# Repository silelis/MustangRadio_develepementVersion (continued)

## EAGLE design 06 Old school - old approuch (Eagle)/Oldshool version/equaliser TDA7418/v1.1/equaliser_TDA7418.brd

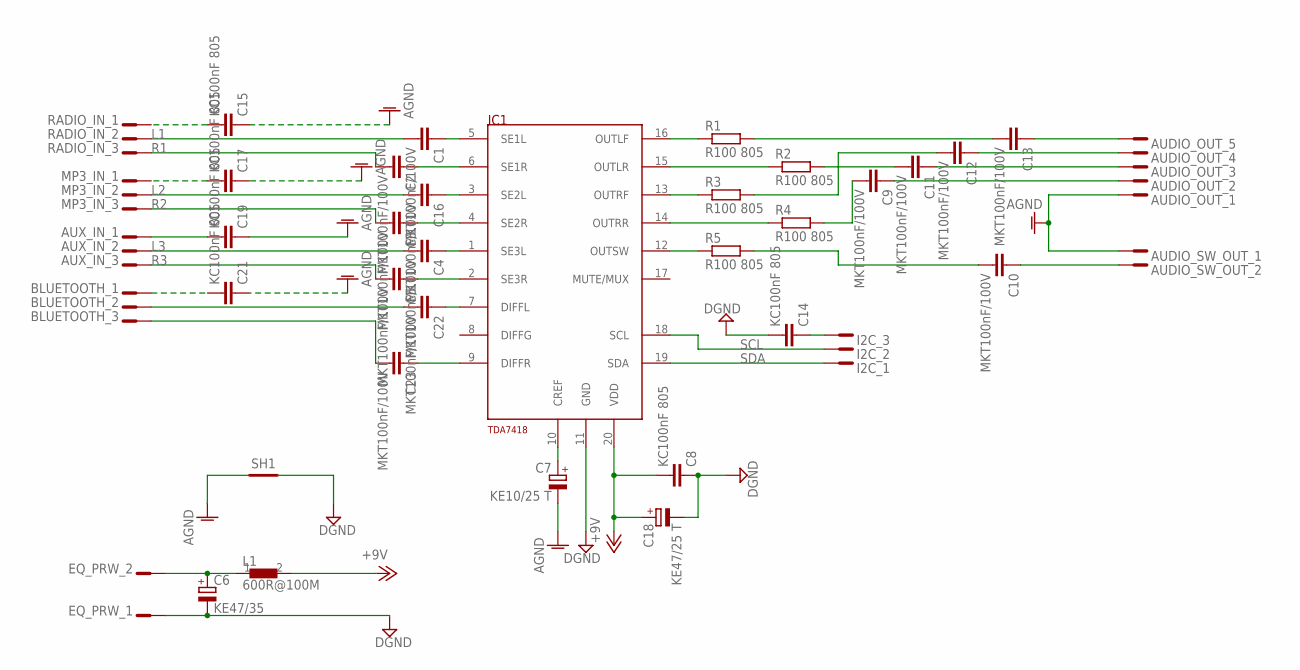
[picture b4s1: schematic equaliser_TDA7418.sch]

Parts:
AUDIO_OUT: JST_5_PIN_B5B-PH-KS; B5B-PH-KS
AUDIO_SW_OUT: JST_2_PIN_B2B-PH-KS; B2B-PH-KS
AUX_IN: JST_3_PIN_B3B-PH-KS; B3B-PH-KS
BLUETOOTH: JST_3_PIN_B3B-PH-KS; B3B-PH-KS
C1, C2, C3, C4, C5, C9, C10, C11, C12, C13, C16, C22, C23: MKT100nF/100V; C050-035X075
C6: KE47/35; TT2D6
C7: KE10/25 T; E1,8-4
C8, C14, C15, C17, C19, C21: KC100nF 805; C0805
C18: KE47/25 T; B45181B
EQ_PRW: JST_2_PIN_B2B-XH-A; B2B-XH-A
I2C: JST_3_PIN_B3B-PH-KS; B3B-PH-KS
IC1: TDA7418; SO20
L1: 600R@100M; R0805
MP3_IN: JST_3_PIN_B3B-PH-KS; B3B-PH-KS
R1, R2, R5: R100 805; R0805
R3, R4: R100 805; M0805
RADIO_IN: JST_3_PIN_B3B-PH-KS; B3B-PH-KS
SH1: SHORT-HT5; SHORT_TOP-50

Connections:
+9V0: C8.2, C18.+, IC1.20 (VDD), L1.2
AGND: AUDIO_OUT.P$1, AUDIO_SW_OUT.P$1, C7.-, C15.1, C17.1, C19.1, C21.1, SH1.1
DGND: C6.-, C8.1, C14.2, C18.-, EQ_PRW.P$1, IC1.11 (GND), SH1.2
L1: C1.2, RADIO_IN.P$2
L2: C16.2, MP3_IN.P$2
L3: AUX_IN.P$2, C4.2
unnamed: C6.+, EQ_PRW.P$2, L1.1
unnamed: AUDIO_OUT.P$2, C9.1
unnamed: C7.+, IC1.10 (CREF)
unnamed: C1.1, IC1.5 (SE1L)
unnamed: C2.1, IC1.6 (SE1R)
unnamed: C16.1, IC1.3 (SE2L)
unnamed: C3.1, IC1.4 (SE2R)
unnamed: C4.1, IC1.1 (SE3L)
unnamed: C5.1, IC1.2 (SE3R)
unnamed: C10.2, R5.2
unnamed: AUDIO_SW_OUT.P$2, C10.1
unnamed: IC1.16 (OUTLF), R1.1
unnamed: IC1.15 (OUTLR), R2.1
unnamed: C12.2, R3.2
unnamed: C11.2, R2.2
unnamed: IC1.13 (OUTRF), R3.1
unnamed: C9.2, R4.2
unnamed: IC1.14 (OUTRR), R4.1
unnamed: IC1.12 (OUTSW), R5.1
unnamed: AUDIO_OUT.P$3, C11.1
unnamed: AUDIO_OUT.P$4, C12.1
unnamed: AUDIO_OUT.P$5, C13.1
unnamed: C14.1, I2C.P$3
unnamed: C15.2, RADIO_IN.P$1
unnamed: C13.2, R1.2
unnamed: C17.2, MP3_IN.P$1
unnamed: AUX_IN.P$1, C19.2
unnamed: BLUETOOTH.P$1, C21.2
unnamed: C22.1, IC1.7 (DIFFL)
unnamed: C23.1, IC1.9 (DIFFR)
unnamed: BLUETOOTH.P$2, C22.2
unnamed: BLUETOOTH.P$3, C23.2
R1: C2.2, RADIO_IN.P$3
R2: C3.2, MP3_IN.P$3
R3: AUX_IN.P$3, C5.2
SCL: I2C.P$2, IC1.18 (SCL)
SDA: I2C.P$1, IC1.19 (SDA)

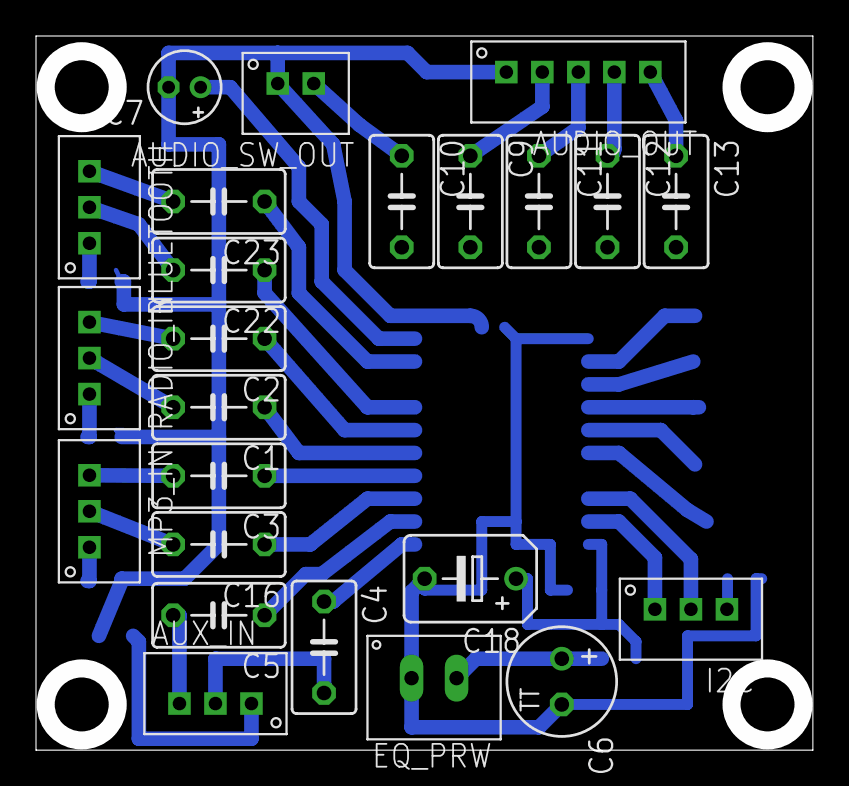
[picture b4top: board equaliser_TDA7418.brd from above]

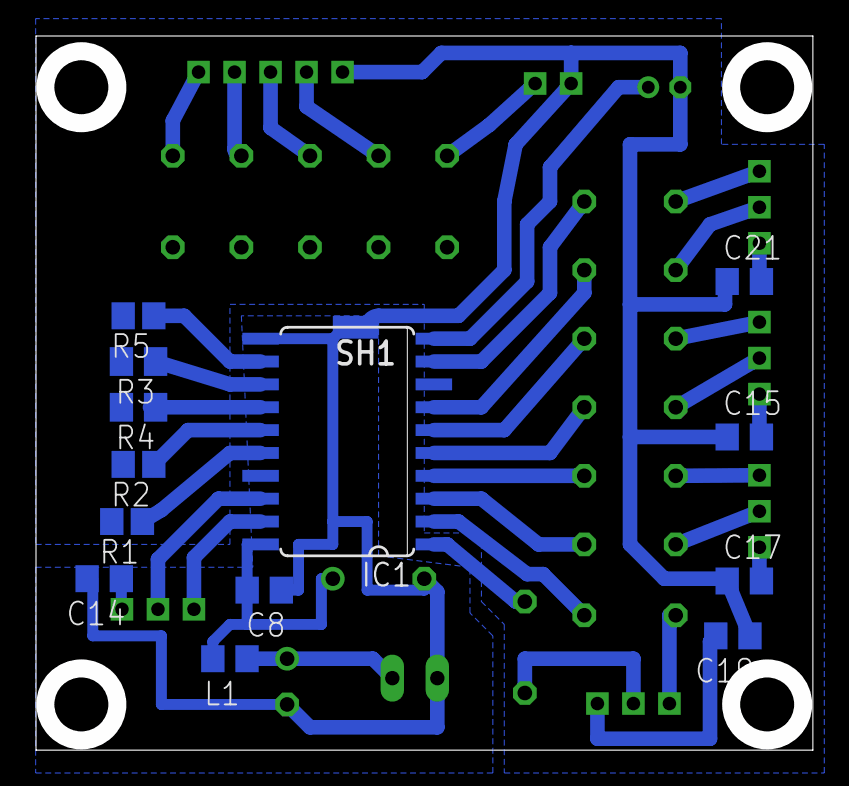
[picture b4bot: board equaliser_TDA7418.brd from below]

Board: 2 copper layers, 43.2 x 39.7 mm, 38 parts (14 on the bottom side), 43 nets.

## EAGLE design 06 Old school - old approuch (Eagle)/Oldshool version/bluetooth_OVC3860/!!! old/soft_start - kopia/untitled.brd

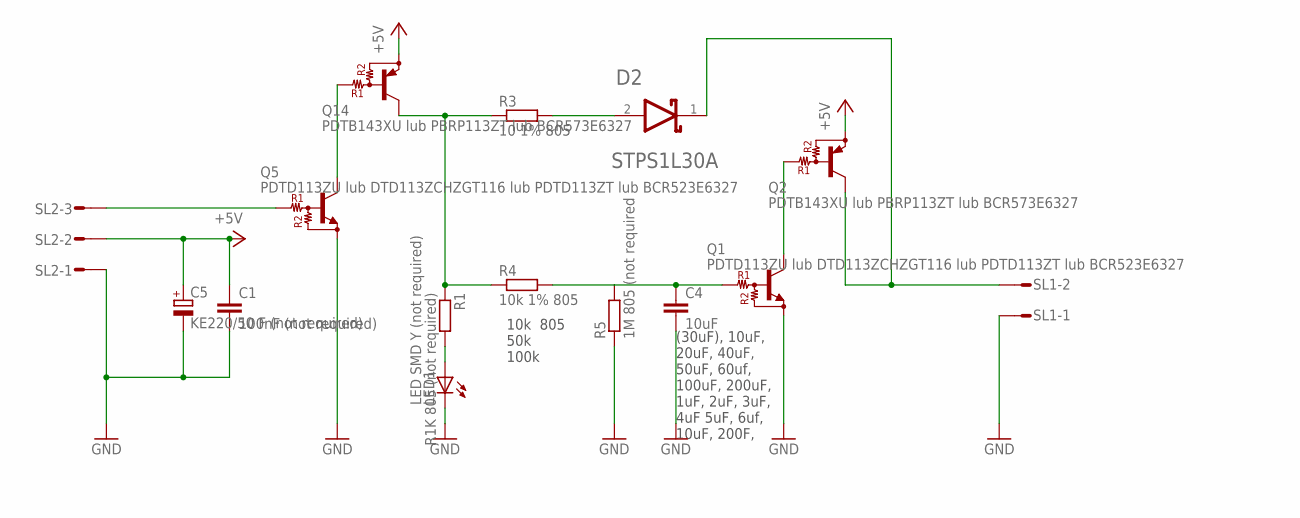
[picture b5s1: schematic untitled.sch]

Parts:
C1: 100nF (not required); C0805
C4: 10uF; C0805
C5: KE220/50 F (not required); PANASONIC_G
D2: MBR0530T1G, STPS1L30A lub STPS1L30U; STMICROELECTRONICS_STPS1L30A_0
LED1: LED SMD Y (not required); CHIP-LED0805
Q1, Q5: PDTD113ZU lub DTD113ZCHZGT116 lub PDTD113ZT lub B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; SOT-23
Q2, Q14: PDTB143XU lub PBRP113ZT lub BCR573E6327; SOT-23
R1: R1K 805 (not required); R0805
R3: 10 1% 805; M0805
R4: 10k 1% 805; M0805
R5: 1M 805 (not required; M0805
SL1: M02S; 02P
SL2: M03S; 03P

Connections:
+5V: C1.1, C5.+, Q2.2 (E), Q14.2 (E), SL2.2
GND: C1.2, C4.2, C5.-, LED1.C, Q1.2 (E), Q5.2 (E), R5.1, SL1.1, SL2.1
unnamed: Q1.3 (C), Q2.1 (B)
unnamed: LED1.A, R1.2
unnamed: Q14.3 (C), R1.1, R3.1, R4.1
unnamed: D2.2 (ANODE), R3.2
unnamed: Q5.1 (B), SL2.3
unnamed: Q5.3 (C), Q14.1 (B)
unnamed: C4.1, Q1.1 (B), R4.2, R5.2
SOFT_START_5.0V: D2.1 (CATHODE), Q2.3 (C), SL1.2

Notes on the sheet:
10k 805 50k 100k
(30uF), 10uF, 20uF, 40uF, 50uF, 60uf, 100uF, 200uF, 1uF, 2uF, 3uF, 4uF 5uF, 6uf, 10uF, 200F,

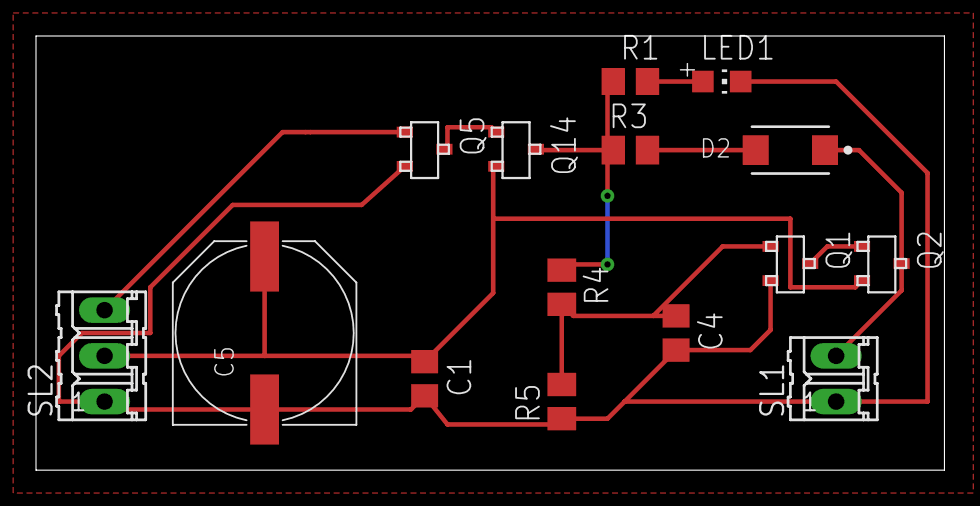
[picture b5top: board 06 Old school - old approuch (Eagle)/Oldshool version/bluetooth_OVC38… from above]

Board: 2 copper layers, 50.5 x 24.1 mm, 15 parts (0 on the bottom side), 10 nets.

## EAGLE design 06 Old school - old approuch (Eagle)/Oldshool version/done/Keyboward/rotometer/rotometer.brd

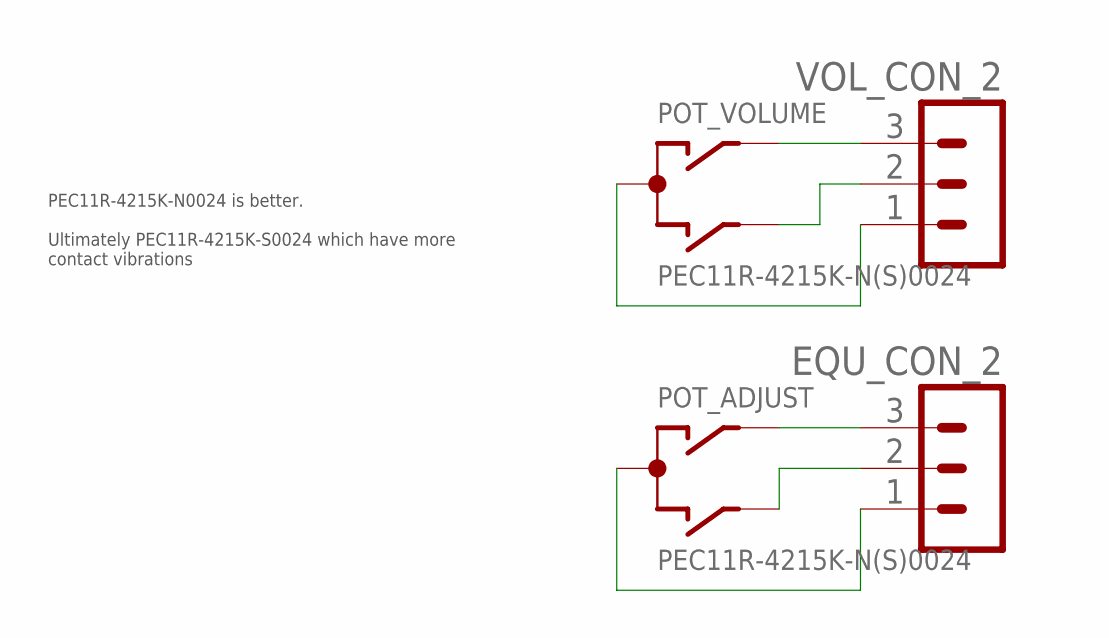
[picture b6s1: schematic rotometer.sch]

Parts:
EQU_CON_2: MA03-1
POT_ADJUST: PEC11R-4215K-N(S)0024; ALPS_EC12E_SW
POT_VOLUME: PEC11R-4215K-N(S)0024; ALPS_EC12E_SW
VOL_CON_2: MA03-1

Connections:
EQU_GND: EQU_CON_2.1, POT_ADJUST.C
unnamed: POT_VOLUME.B, VOL_CON_2.2
unnamed: POT_VOLUME.A, VOL_CON_2.3
unnamed: EQU_CON_2.3, POT_ADJUST.A
unnamed: EQU_CON_2.2, POT_ADJUST.B
VOL_GND: POT_VOLUME.C, VOL_CON_2.1

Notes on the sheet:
PEC11R-4215K-N0024 is better. Ultimately PEC11R-4215K-S0024 which have more contact vibrations

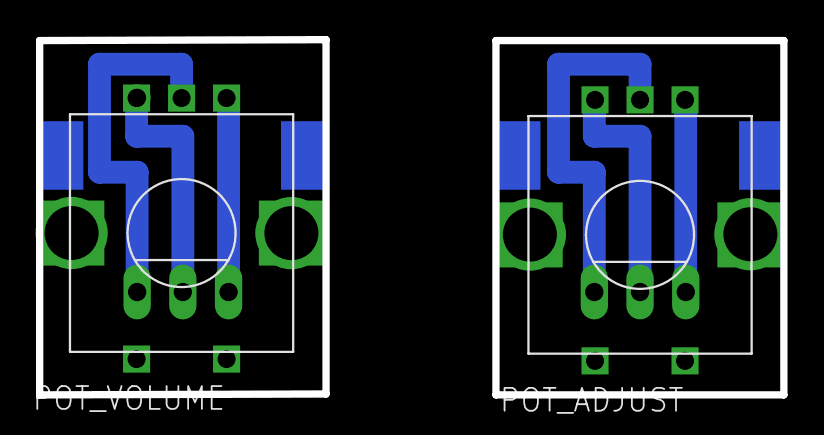
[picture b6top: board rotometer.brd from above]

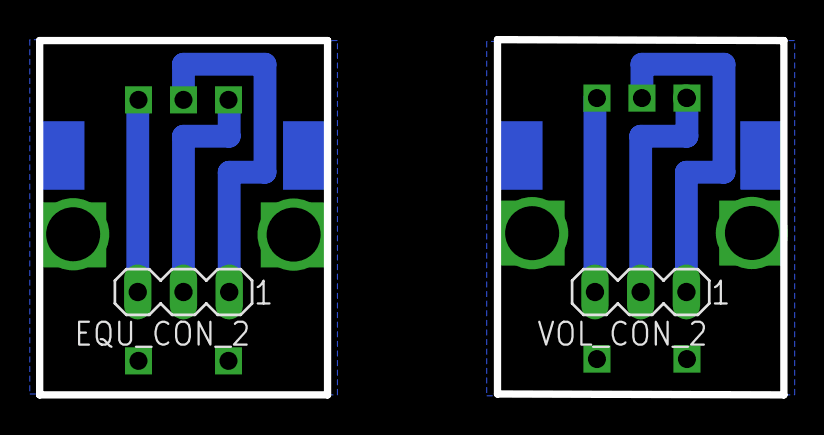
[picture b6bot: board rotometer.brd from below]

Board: 2 copper layers, 41.3 x 19.7 mm, 4 parts (2 on the bottom side), 6 nets.

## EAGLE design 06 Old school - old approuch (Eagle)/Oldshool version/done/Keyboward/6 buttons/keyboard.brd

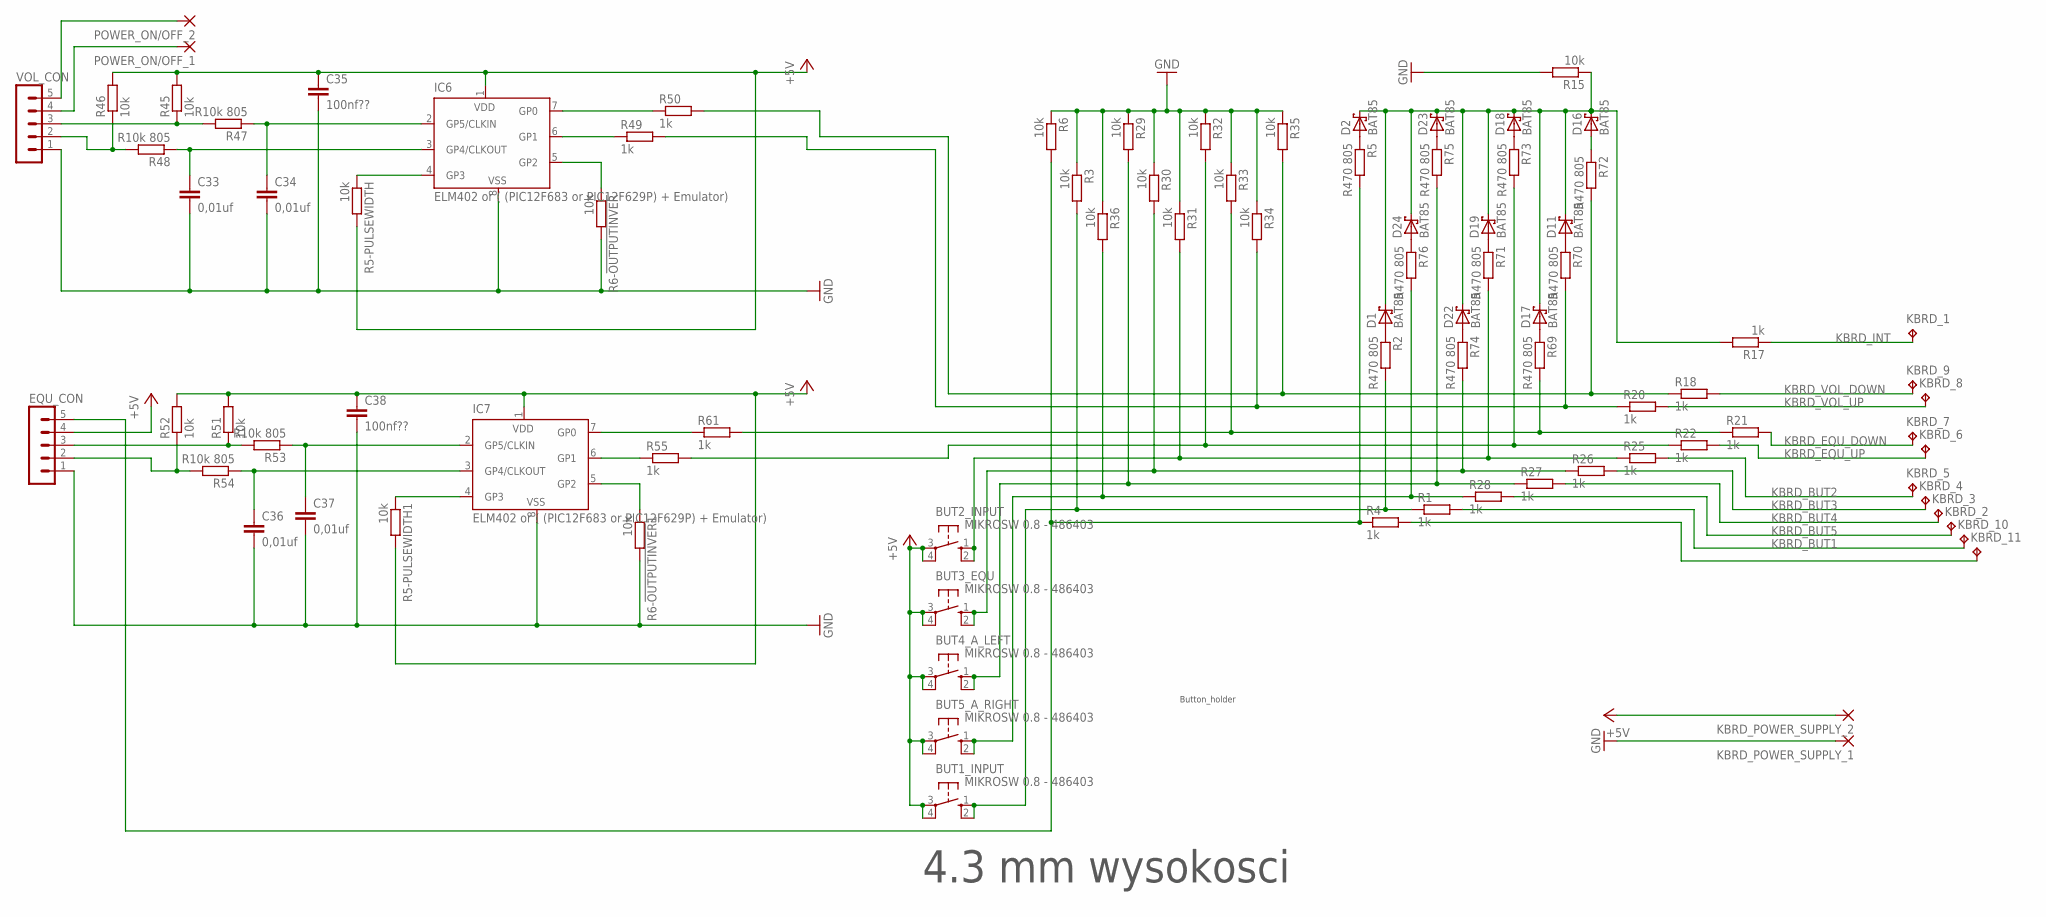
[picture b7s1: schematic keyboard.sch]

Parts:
BUT1_INPUT, BUT2_INPUT, BUT3_EQU, BUT4_A_LEFT, BUT5_A_RIGHT: MIKROSW 0.8 - 486403; B3F-10XX; MPN B3F-1000
C33, C34, C36, C37: 0,01uf; C0805
C35, C38: 100nf??; C0805
D1, D2, D11, D16, D17, D18, D19, D22, D23, D24: BAT85; DO34-5
EQU_CON: MA05-1
IC6, IC7: ELM402 or ( (PIC12F683 or PIC12F629P) + Emulator); DIL8; MPN PIC12F629-E/P
KBRD_1, KBRD_2, KBRD_3, KBRD_4, KBRD_5, KBRD_6, KBRD_7, KBRD_8, KBRD_9, KBRD_10, KBRD_11: TPPAD1-13Y; P1-13Y
KBRD_POWER_SUPPLY_1, KBRD_POWER_SUPPLY_2: 1,6/0,9
POWER_ON/OFF_1, POWER_ON/OFF_2: 2,15/1,0
R1, R4, R17, R18, R20, R21, R22, R25, R26, R27, R28, R49, R50, R55, R61: 1k; R0805
R2, R5, R69, R70, R71, R72, R73, R74, R75, R76: R470 805; R0805
R3, R6-!OUTPUTINVER!, R6-!OUTPUTINVER!1, R15, R29, R30, R36, R45, R46: 10k; R0805
R5-PULSEWIDTH, R5-PULSEWIDTH1: 10k; 0204/7
R6, R32, R33, R34, R35: 10k; 0204/5
R31, R51, R52: 10k; M0805
R47, R48, R53, R54: R10k 805; R0805
U$1: TRZYMADLO; TRZYMADLO_POPYCHACZY
VOL_CON: MA05-1

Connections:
+5V: BUT1_INPUT.3, BUT1_INPUT.4 (P1), BUT2_INPUT.3, BUT2_INPUT.4 (P1), BUT3_EQU.3, BUT3_EQU.4 (P1), BUT4_A_LEFT.3, BUT4_A_LEFT.4 (P1), BUT5_A_RIGHT.3, BUT5_A_RIGHT.4 (P1), C35.1, C38.1, EQU_CON.4, IC6.1 (VDD), IC7.1 (VDD), KBRD_POWER_SUPPLY_2.1, R5-PULSEWIDTH.2, R5-PULSEWIDTH1.2, R45.2, R46.2, R51.2, R52.2
GND: C33.2, C34.2, C35.2, C36.2, C37.2, C38.2, EQU_CON.1, IC6.8 (VSS), IC7.8 (VSS), KBRD_POWER_SUPPLY_1.1, R3.1, R6.1, R6-!OUTPUTINVER!.2, R6-!OUTPUTINVER!1.2, R15.2, R29.1, R30.1, R31.1, R32.1, R33.1, R34.1, R35.1, R36.1, VOL_CON.1
KBRD_BUT1: KBRD_10.TP, R1.2
KBRD_BUT2: KBRD_5.TP, R25.2
KBRD_BUT3: KBRD_4.TP, R26.2
KBRD_BUT4: KBRD_3.TP, R27.2
KBRD_BUT5: KBRD_2.TP, R28.2
KBRD_EQU_BUT: KBRD_11.TP, R4.2
KBRD_EQU_DOWN: KBRD_7.TP, R21.2
KBRD_EQU_UP: KBRD_6.TP, R22.2
KBRD_INT: KBRD_1.TP, R17.1
KBRD_VOL_DOWN: KBRD_9.TP, R18.2
KBRD_VOL_UP: KBRD_8.TP, R20.2
unnamed: R20.1, R34.2, R49.2, R70.2
unnamed: R18.1, R35.2, R50.2, R72.2
unnamed: R22.1, R32.2, R55.2, R73.2
unnamed: R21.1, R33.2, R61.2, R69.2
unnamed: R46.1, R48.2, VOL_CON.2
unnamed: R45.1, R47.2, VOL_CON.3
unnamed: D2.A, R5.1
unnamed: POWER_ON/OFF_2.1, VOL_CON.5
unnamed: BUT1_INPUT.1 (S), BUT1_INPUT.2 (S1), R1.1, R2.2, R3.2
unnamed: EQU_CON.2, R52.1, R54.2
unnamed: EQU_CON.3, R51.1, R53.2
unnamed: POWER_ON/OFF_1.1, VOL_CON.4
unnamed: D1.A, R2.1
unnamed: EQU_CON.5, R4.1, R5.2, R6.2
unnamed: BUT2_INPUT.1 (S), BUT2_INPUT.2 (S1), R25.1, R31.2, R71.2
unnamed: BUT3_EQU.1 (S), BUT3_EQU.2 (S1), R26.1, R30.2, R74.2
unnamed: BUT4_A_LEFT.1 (S), BUT4_A_LEFT.2 (S1), R27.1, R29.2, R75.2
unnamed: BUT5_A_RIGHT.1 (S), BUT5_A_RIGHT.2 (S1), R28.1, R36.2, R76.2
unnamed: C34.1, IC6.2 (GP5/CLKIN), R47.1
unnamed: C33.1, IC6.3 (GP4/CLKOUT), R48.1
unnamed: IC6.4 (GP3), R5-PULSEWIDTH.1
unnamed: IC6.5 (GP2), R6-!OUTPUTINVER!.1
unnamed: IC6.6 (GP1), R49.1
unnamed: IC6.7 (GP0), R50.1
unnamed: C37.1, IC7.2 (GP5/CLKIN), R53.1
unnamed: C36.1, IC7.3 (GP4/CLKOUT), R54.1
unnamed: IC7.4 (GP3), R5-PULSEWIDTH1.1
unnamed: IC7.5 (GP2), R6-!OUTPUTINVER!1.1
unnamed: IC7.6 (GP1), R55.1
unnamed: IC7.7 (GP0), R61.1
unnamed: D17.A, R69.1
unnamed: D11.A, R70.1
unnamed: D18.A, R73.1
unnamed: D19.A, R71.1
unnamed: D22.A, R74.1
unnamed: D23.A, R75.1
unnamed: D24.A, R76.1
unnamed: D1.C, D2.C, D11.C, D16.C, D17.C, D18.C, D19.C, D22.C, D23.C, D24.C, R15.1, R17.2
unnamed: D16.A, R72.1

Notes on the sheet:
4.3 mm wysokosci

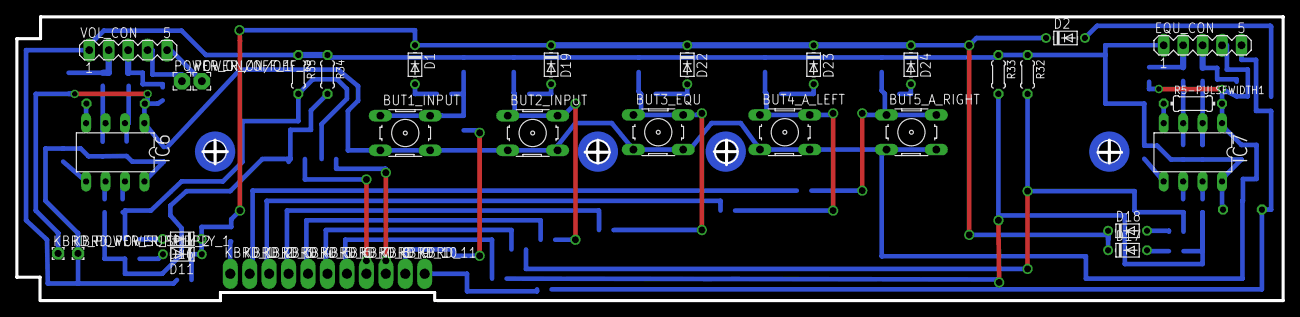
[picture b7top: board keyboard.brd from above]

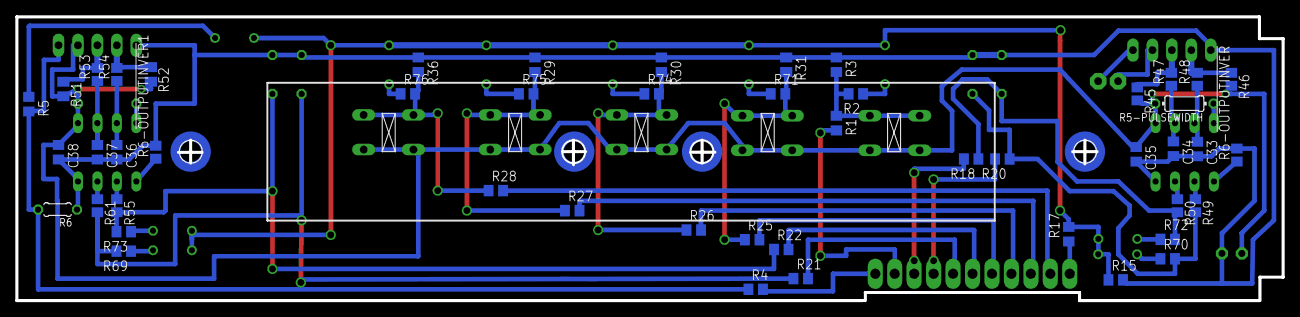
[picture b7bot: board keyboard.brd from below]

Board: 2 copper layers, 165.4 x 37.1 mm, 89 parts (50 on the bottom side), 52 nets.

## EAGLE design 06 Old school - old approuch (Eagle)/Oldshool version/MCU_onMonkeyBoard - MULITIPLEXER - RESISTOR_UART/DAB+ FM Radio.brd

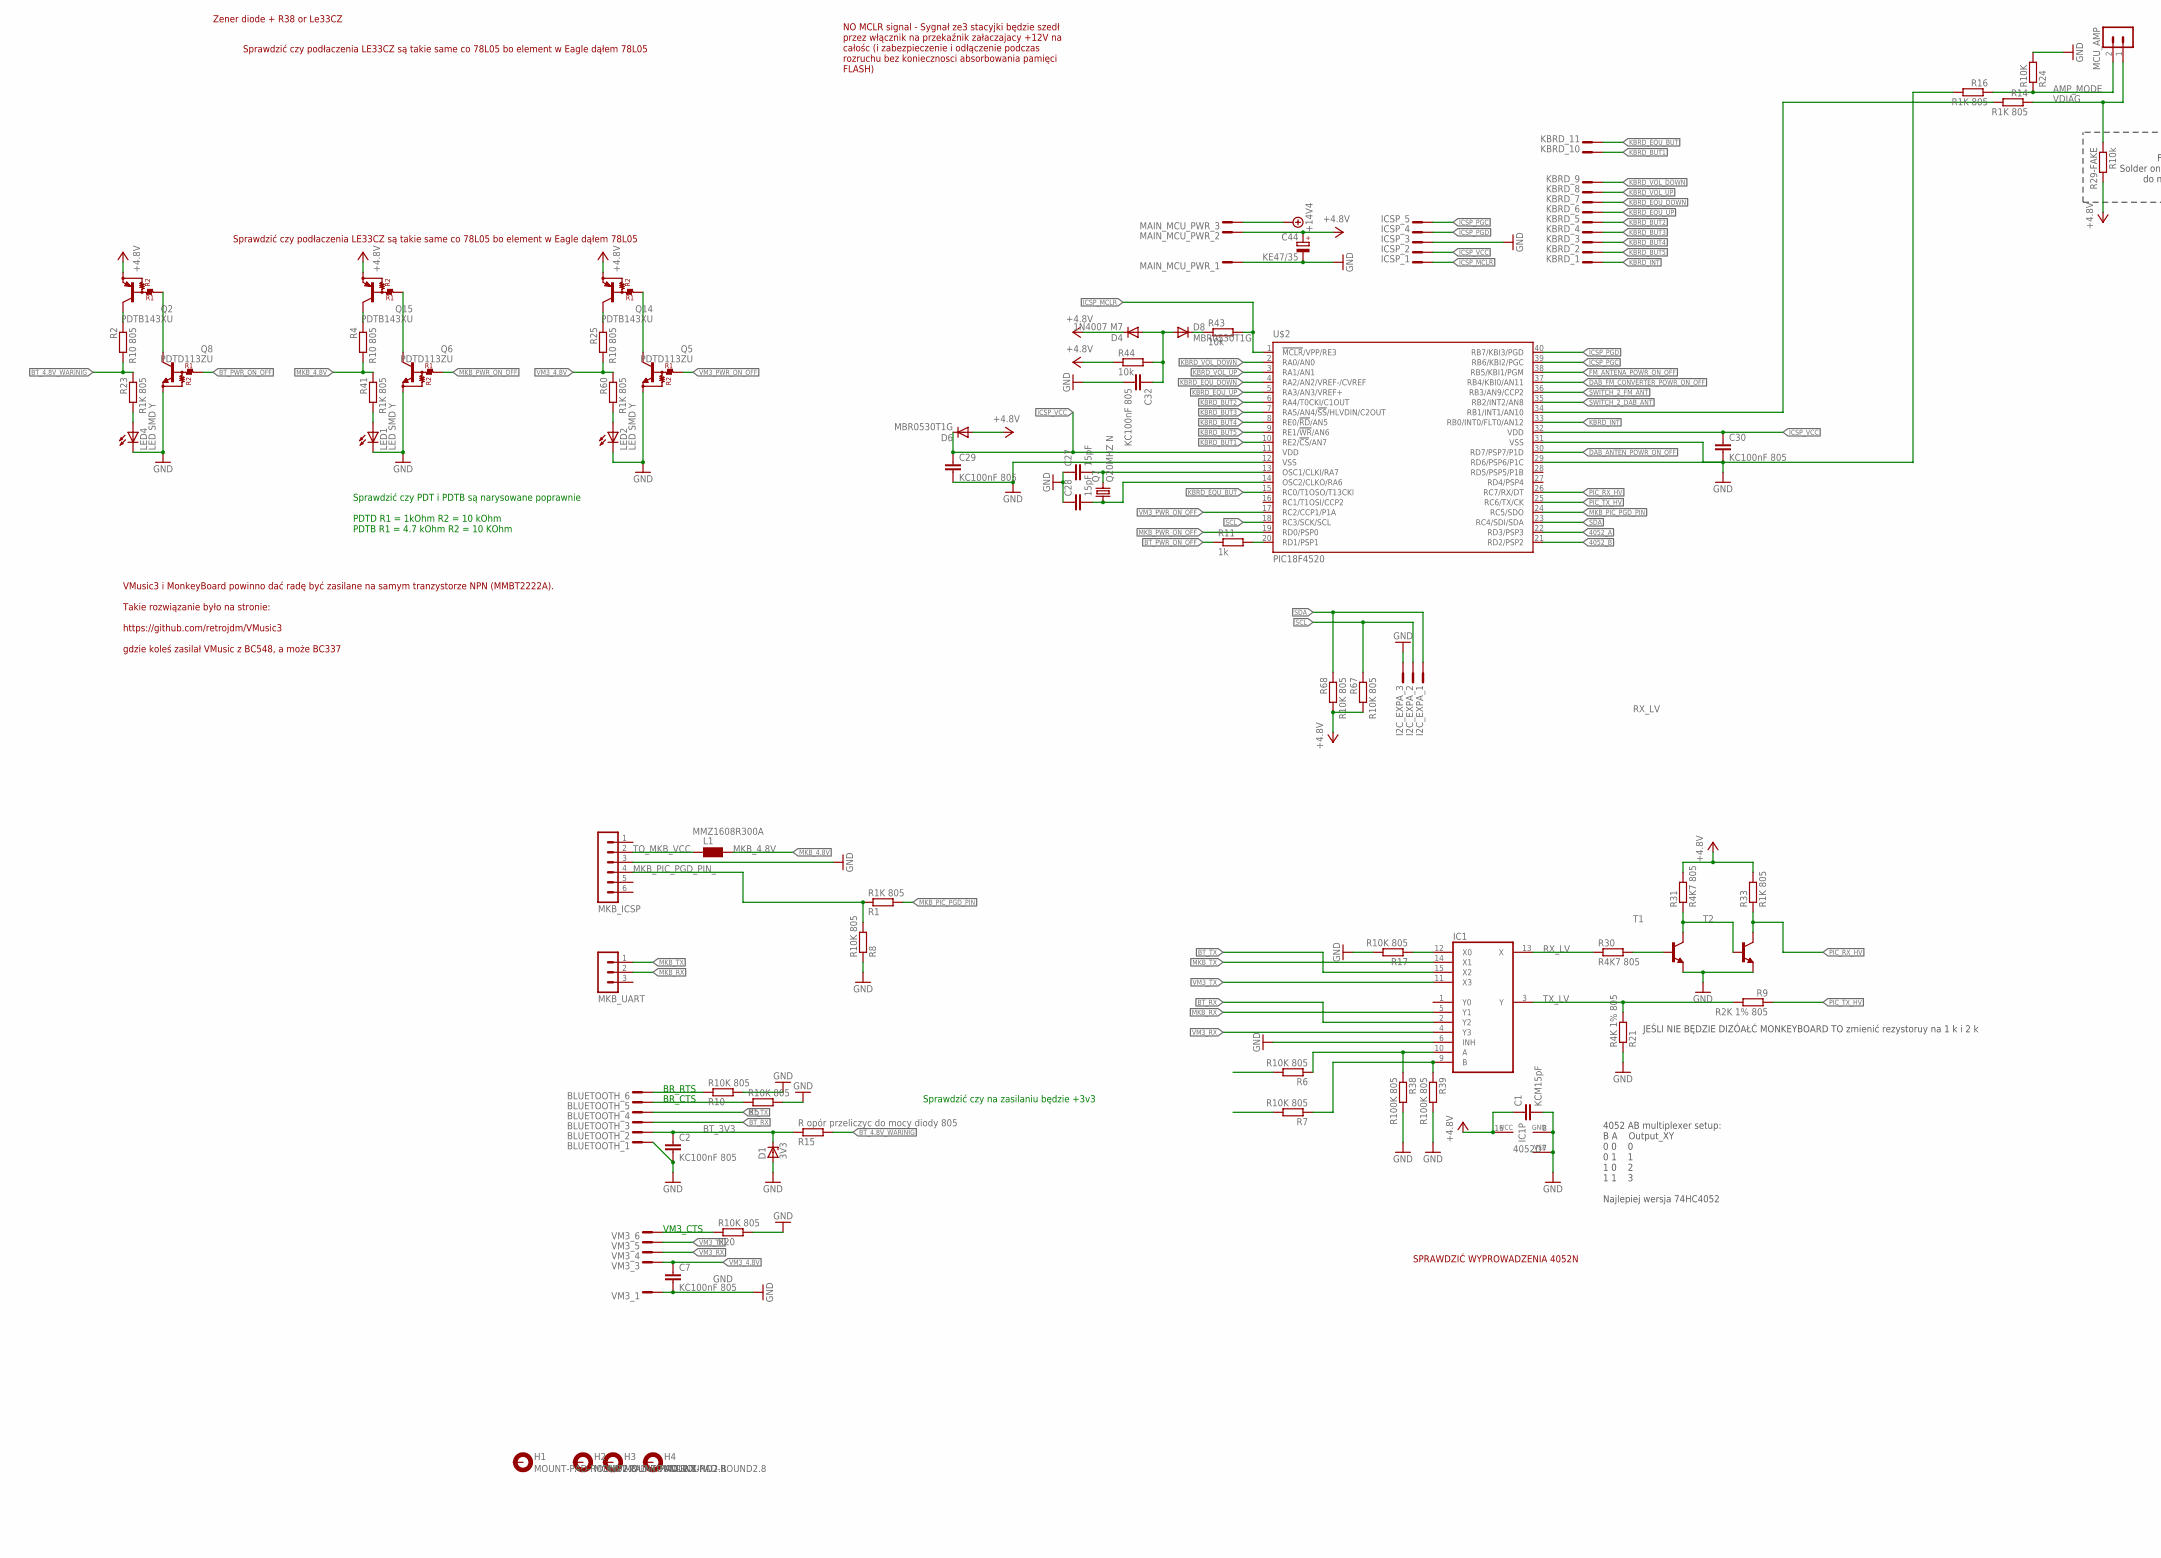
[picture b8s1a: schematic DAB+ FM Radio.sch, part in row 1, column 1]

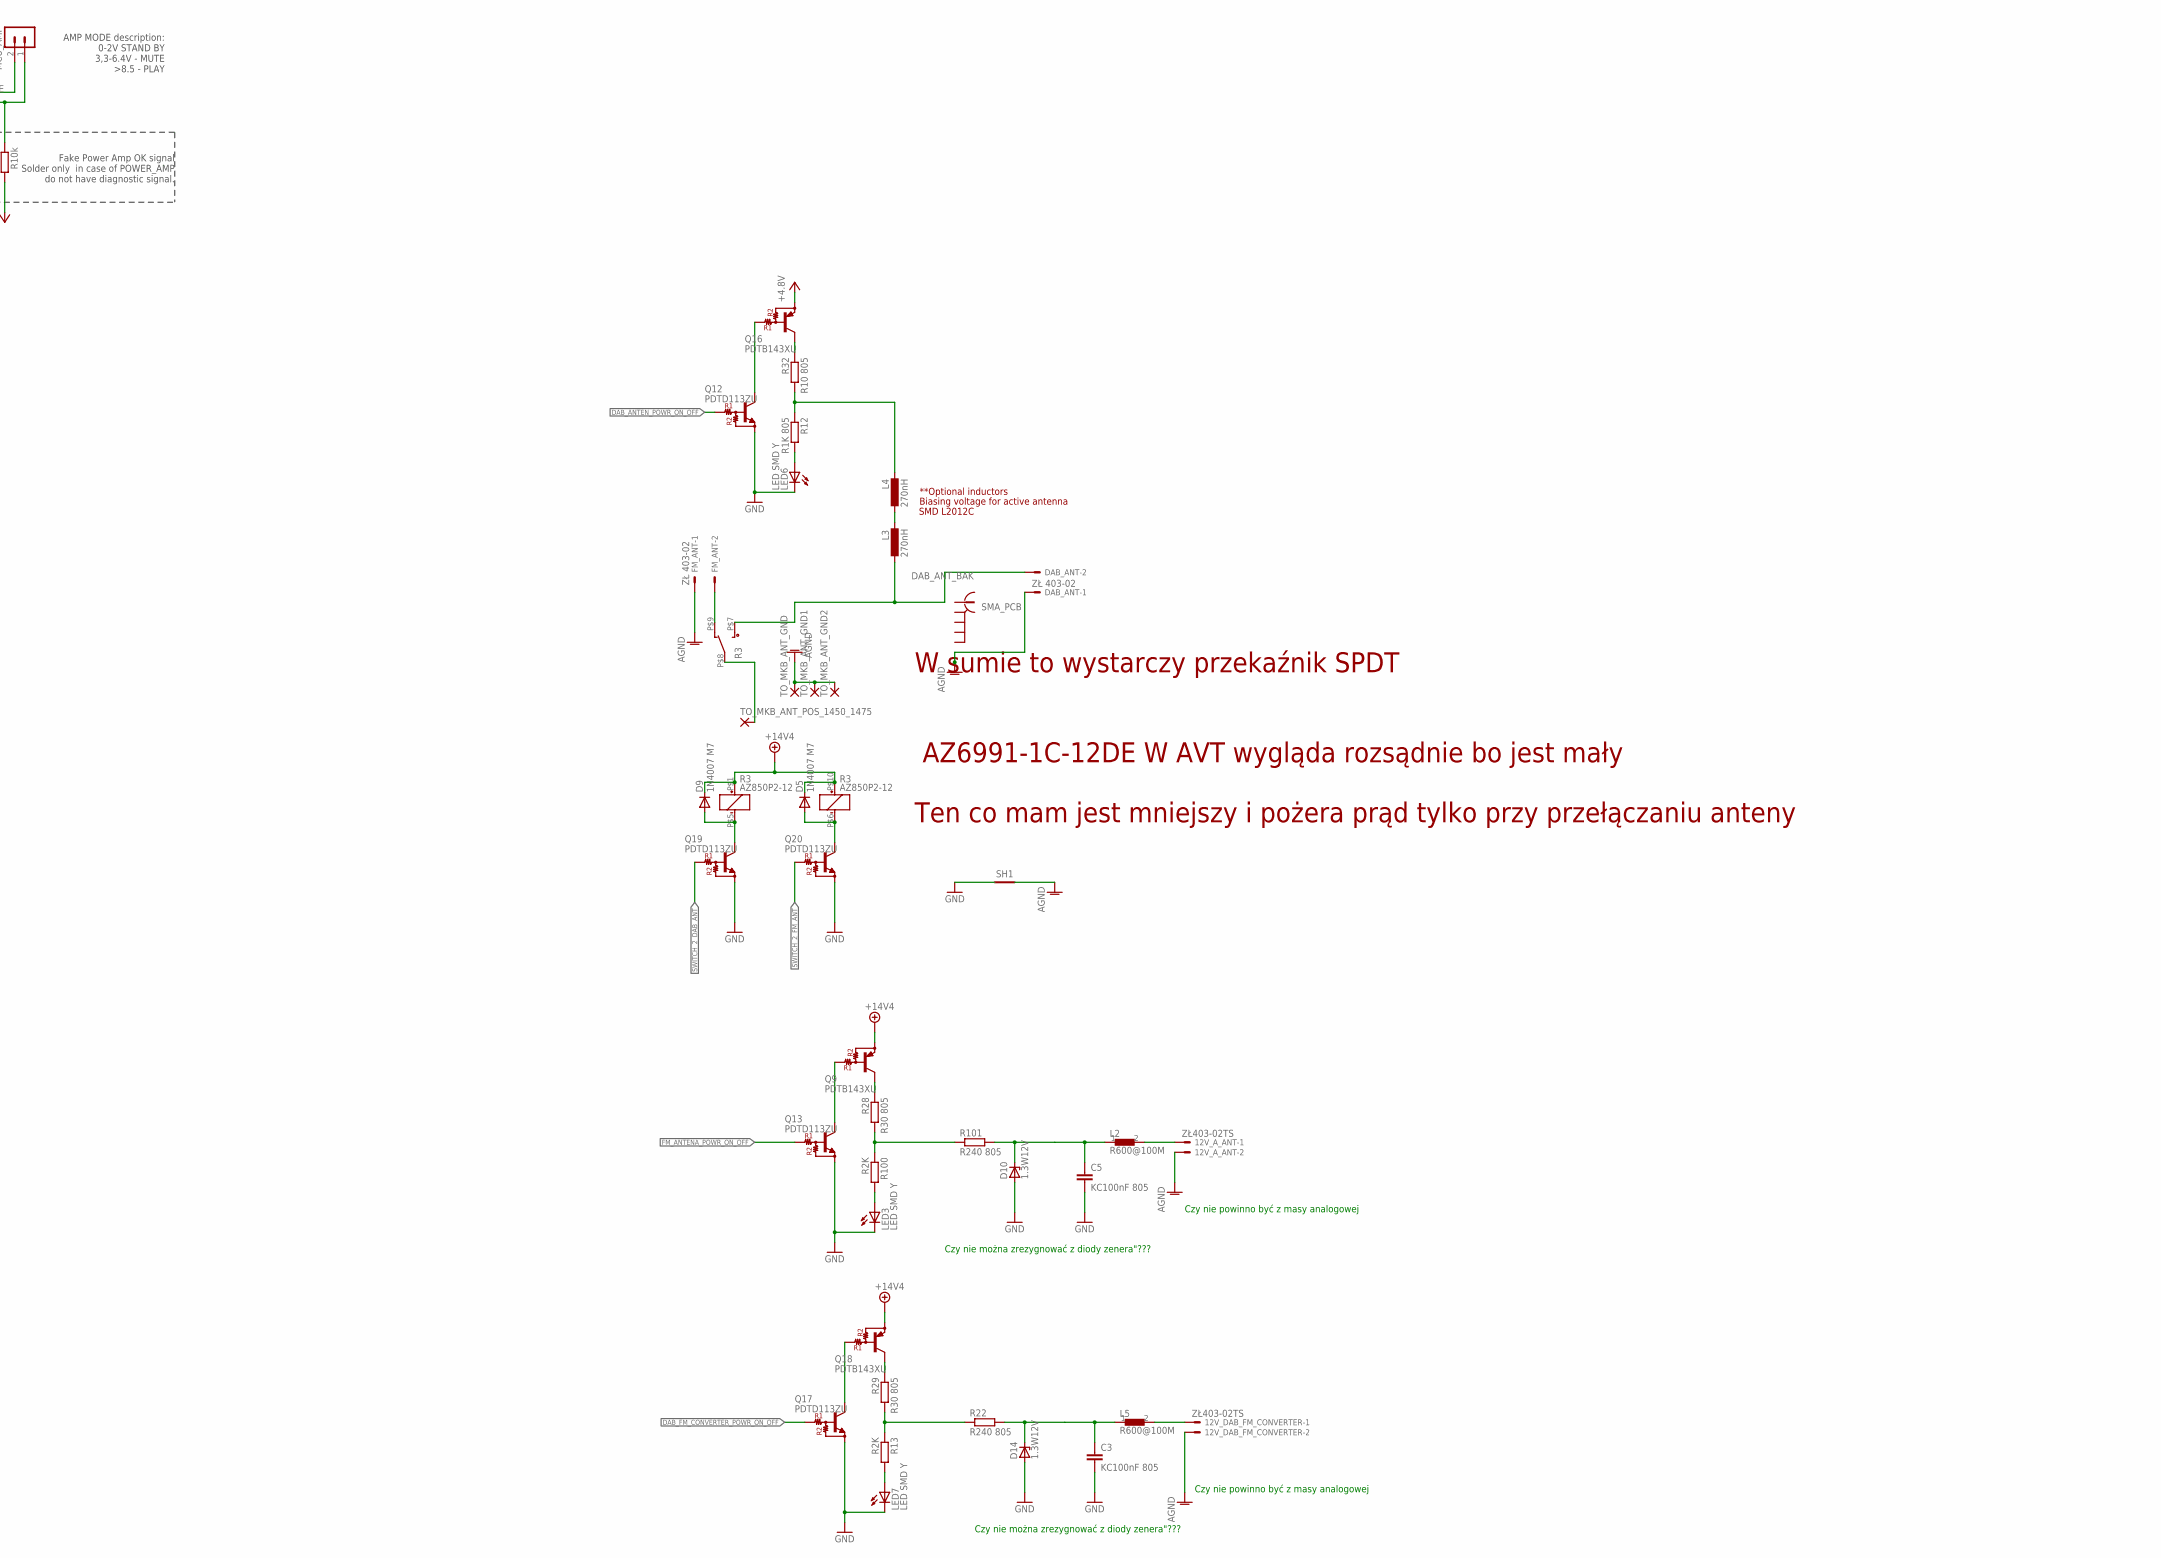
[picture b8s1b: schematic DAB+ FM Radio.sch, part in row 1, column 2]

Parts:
12V_A_ANT, 12V_DAB_FM_CONVERTER: ZŁ403-02TS; 22-23-2021
BLUETOOTH: JST_6_PIN_B6B-PH-KS; B6B-PH-KS
C1: KCM15pF; C0805
C2, C3, C5, C7, C29, C30, C32: KC100nF 805; C0805
C27, C28: 15pF; C0805
C44: KE47/35; TT2D6
D1: 3V3; SOD80C
D4, D5, D9: 1N4007 M7; SOD-123_MINI-SMA
D6, D8: MBR0530T1G; SOD123
D10, D14: 1.3W12V; ZDIO-2.5
DAB_ANT: ZŁ 403-02; 6410-02
DAB_ANT_BAK: SMA_PCB
FM_ANT: ZŁ 403-02; 6410-02
H1, H2, H3, H4: MOUNT-PAD-ROUND2.8; 2,8-PAD
I2C_EXPA: JST_3_PIN_B3B-PH-KS; B3B-PH-KS
IC1: 4052D; SO16
ICSP: JST_5_PIN_B5B-PH-KS; B5B-PH-KS
KBRD: JST_11_PIN_B11B-PH-KS; B11B-PH-KS
L1: MMZ1608R300A; 0603
L2, L5: R600@100M; R0805
L3, L4: 270nH; L2012C
LED1, LED2, LED4: LED SMD Y; CHIP-LED0805
LED3, LED6, LED7: LED SMD Y; SMARTLED-TTW
MAIN_MCU_PWR: JST_3_PIN_B3B-XH-A; B3B-XH-A
MCU_AMP: MA02-1
MKB_ICSP: MA06-1
MKB_UART: MA03-1
Q2, Q9, Q14, Q15, Q16, Q18: PDTB143XU; SOT-23
Q5, Q6, Q8, Q12, Q13, Q17, Q19, Q20: PDTD113ZU; SOT-23
Q7: Q20MHZ N; HC49/S
R1, R12, R14, R16, R23, R33, R41, R60: R1K 805; R0805
R2, R4, R25, R32: R10 805; R0805
R3: AZ850P2-12; AZ850-2C
R5, R6, R7, R8, R10, R17, R20, R67, R68: R10K 805; R0805
R9: R2K 1% 805; R0805
R11: 1k; R0805
R13, R100: R2K; R0805
R15: R opór przeliczyc do mocy diody 805; R0805
R21: R4K 1% 805; R0805
R22, R101: R240 805; M0805
R24: R10K; R0805
R28, R29: R30 805; R0805
R29-FAKE: R10k; M0805
R30, R31: R4K7 805; R0805
R38, R39: R100K 805; M0805
R43: 10k; R0805
R44: 10k; M0805
SH1: SHORT-HT5; SHORT_TOP-50
T1, T2: MMBT2222ALT1-NPN-SOT23-BEC; SOT23-BEC
TO_MKB_ANT_GND, TO_MKB_ANT_GND1, TO_MKB_ANT_GND2: 2,54/0,8
TO_MKB_ANT_POS_1450_1475: 2,54/0,8
U$2: PIC18F4520; DIL40
VM3: JST_6_PIN_B6B-PH-KS; B6B-PH-KS

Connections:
4052_A: R6.2, U$2.22 (RD3/PSP3)
4052_B: R7.2, U$2.21 (RD2/PSP2)
+5V: C1.1, C44.+, D4.C, D6.A, IC1.16 (VCC), MAIN_MCU_PWR.P$2, Q2.2 (E), Q14.2 (E), Q15.2 (E), Q16.2 (E), R29-FAKE.2, R31.2, R33.2, R44.1, R67.2, R68.2
+14V4: D5.C, D9.C, MAIN_MCU_PWR.P$3, Q9.2 (E), Q18.2 (E), R3.P$1 (+), R3.P$10 (+)
AGND: 12V_A_ANT.2, 12V_DAB_FM_CONVERTER.2, DAB_ANT.1, FM_ANT.1, SH1.2, TO_MKB_ANT_GND.1, TO_MKB_ANT_GND1.1, TO_MKB_ANT_GND2.1
AMP_MODE: MCU_AMP.2, R16.1, R24.1
BT_3V3: BLUETOOTH.P$2, C2.1, D1.C, R15.1
BT_4.8V_WARINIG: R2.2, R15.2, R23.1
BT_PWR_ON_OFF: Q8.1 (B), R11.1
BT_RX: BLUETOOTH.P$3, IC1.2 (Y2)
BT_TX: BLUETOOTH.P$4, IC1.15 (X2)
DAB_ANTEN_POWR_ON_OFF: Q12.1 (B), U$2.30 (RD7/PSP7/P1D)
DAB_FM_CONVERTER_POWR_ON_OFF: Q17.1 (B), U$2.37 (RB4/KBI0/AN11)
FM_ANTENA_POWR_ON_OFF: Q13.1 (B), U$2.38 (RB5/KBI1/PGM)
GND: BLUETOOTH.P$1, C1.2, C2.2, C3.2, C5.2, C7.2, C27.1, C28.1, C29.2, C30.2, C32.2, C44.-, D1.A, D10.A, D14.A, DAB_ANT_BAK.GND@1 (GND), DAB_ANT_BAK.GND@2 (GND), DAB_ANT_BAK.GND@3 (GND), DAB_ANT_BAK.GND@4 (GND), I2C_EXPA.P$3, IC1.6 (INH), IC1.7 (VEE), IC1.8 (GND), ICSP.P$3, LED1.C, LED2.C, LED3.C@1 (C), LED4.C, LED6.C@1 (C), LED7.C@1 (C), MAIN_MCU_PWR.P$1, MKB_ICSP.3, Q5.2 (E), Q6.2 (E), Q8.2 (E), Q12.2 (E), Q13.2 (E), Q17.2 (E), Q19.2 (E), Q20.2 (E), R5.2, R8.1, R10.2, R17.2, R20.2, R21.1, R24.2, R38.2, R39.2, SH1.1, T1.E, T2.E, U$2.12 (VSS), U$2.31 (VSS), VM3.P$1
ICSP_MCLR: ICSP.P$1, R43.2, U$2.1 (!MCLR!/VPP/RE3)
ICSP_PGC: ICSP.P$5, U$2.39 (RB6/KBI2/PGC)
ICSP_PGD: ICSP.P$4, U$2.40 (RB7/KBI3/PGD)
ICSP_VCC: C29.1, C30.1, D6.C, ICSP.P$2, U$2.11 (VDD), U$2.32 (VDD)
KBRD_BUT1: KBRD.P$10, U$2.10 (RE2/!CS!/AN7)
KBRD_BUT2: KBRD.P$5, U$2.6 (RA4/T0CKI/C1OUT)
KBRD_BUT3: KBRD.P$4, U$2.7 (RA5/AN4/!SS!/HLVDIN/C2OUT)
KBRD_BUT4: KBRD.P$3, U$2.8 (RE0/!RD!/AN5)
KBRD_BUT5: KBRD.P$2, U$2.9 (RE1/!WR!/AN6)
KBRD_EQU_BUT: KBRD.P$11, U$2.15 (RC0/T1OSO/T13CKI)
KBRD_EQU_DOWN: KBRD.P$7, U$2.4 (RA2/AN2/VREF-/CVREF)
KBRD_EQU_UP: KBRD.P$6, U$2.5 (RA3/AN3/VREF+)
KBRD_INT: KBRD.P$1, U$2.33 (RB0/INT0/FLT0/AN12)
KBRD_VOL_DOWN: KBRD.P$9, U$2.2 (RA0/AN0)
KBRD_VOL_UP: KBRD.P$8, U$2.3 (RA1/AN1)
MKB_4.8V: L1.2, R4.2, R41.1
MKB_PIC_PGD_PIN: R1.2, U$2.24 (RC5/SDO)
MKB_PIC_PGD_PIN_: MKB_ICSP.4, R1.1, R8.2
MKB_PWR_ON_OFF: Q6.1 (B), U$2.19 (RD0/PSP0)
MKB_RX: IC1.5 (Y1), MKB_UART.2
MKB_TX: IC1.14 (X1), MKB_UART.1
unnamed: L4.1, R12.1, R32.2
unnamed: D9.A, Q19.3 (C), R3.P$5 (-)
unnamed: R3.P$8 (5), TO_MKB_ANT_POS_1450_1475.1
unnamed: DAB_ANT.2, L3.2, R3.P$7 (6)
unnamed: FM_ANT.2, R3.P$9 (4)
unnamed: D5.A, Q20.3 (C), R3.P$6 (-)
unnamed: Q2.3 (C), R2.1
unnamed: R16.2, U$2.29 (RD6/PSP6/P1C)
unnamed: IC1.12 (X0), R17.1
unnamed: R14.2, U$2.34 (RB1/INT1/AN10)
unnamed: R30.2, T1.B
unnamed: L3.1, L4.2
unnamed: IC1.9 (B), R7.1, R39.1
unnamed: R31.1, T1.C, T2.B
unnamed: C27.2, Q7.2, U$2.13 (OSC1/CLKI/RA7)
unnamed: C28.2, Q7.1, U$2.14 (OSC2/CLKO/RA6)
unnamed: R11.2, U$2.20 (RD1/PSP1)
unnamed: Q15.3 (C), R4.1
unnamed: Q2.1 (B), Q8.3 (C)
unnamed: Q12.3 (C), Q16.1 (B)
unnamed: LED4.A, R23.2
unnamed: LED6.A@1 (A), R12.2
unnamed: Q17.3 (C), Q18.1 (B)
unnamed: R13.1, R22.1, R29.2
unnamed: LED7.A@1 (A), R13.2
unnamed: Q5.3 (C), Q14.1 (B)
unnamed: C3.1, D14.C, L5.1, R22.2
unnamed: 12V_DAB_FM_CONVERTER.1, L5.2
unnamed: LED2.A, R60.2
unnamed: Q14.3 (C), R25.1
unnamed: Q16.3 (C), R32.1
unnamed: Q9.3 (C), R28.1
unnamed: Q18.3 (C), R29.1
unnamed: Q6.3 (C), Q15.1 (B)
unnamed: BLUETOOTH.P$5, R5.1
unnamed: LED1.A, R41.2
unnamed: D8.C, R43.1
unnamed: C32.1, D4.A, D8.A, R44.2
unnamed: BLUETOOTH.P$6, R10.1
unnamed: R20.1, VM3.P$6
unnamed: IC1.10 (A), R6.1, R38.1
unnamed: Q9.1 (B), Q13.3 (C)
unnamed: R28.2, R100.1, R101.1
unnamed: LED3.A@1 (A), R100.2
unnamed: C5.1, D10.C, L2.1, R101.2
unnamed: 12V_A_ANT.1, L2.2
PIC_RX_HV: R33.1, T2.C, U$2.26 (RC7/RX/DT)
PIC_TX_HV: R9.1, U$2.25 (RC6/TX/CK)
RX_LV: IC1.13 (X), R30.1
SCL: I2C_EXPA.P$2, R67.1, U$2.18 (RC3/SCK/SCL)
SDA: I2C_EXPA.P$1, R68.1, U$2.23 (RC4/SDI/SDA)
SWITCH_2_DAB_ANT: Q19.1 (B), U$2.35 (RB2/INT2/AN8)
SWITCH_2_FM_ANT: Q20.1 (B), U$2.36 (RB3/AN9/CCP2)
TO_MKB_VCC: L1.1, MKB_ICSP.2
TX_LV: IC1.3 (Y), R9.2, R21.2
VDIAG: MCU_AMP.1, R14.1, R29-FAKE.1
VM3_4.8V: C7.1, R25.2, R60.1, VM3.P$3
VM3_PWR_ON_OFF: Q5.1 (B), U$2.17 (RC2/CCP1/P1A)
VM3_RX: IC1.4 (Y3), VM3.P$4
VM3_TX: IC1.11 (X3), VM3.P$5

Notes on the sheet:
AMP MODE description: 0-2V STAND BY 3,3-6.4V - MUTE >8.5 - PLAY
Fake Power Amp OK signal Solder only in case of POWER_AMP do not have diagnostic signal.
NO MCLR signal - Sygnał ze3 stacyjki będzie szedł przez włącznik na przekaźnik załaczajacy +12V na całośc (i zabezpieczenie i odłączenie podczas rozruchu bez koniecznosci absorbowania pamięci FLASH)
Sprawdzić czy podłaczenia LE33CZ są takie same co 78L05 bo element w Eagle dąłem 78L05
Sprawdzić czy PDT i PDTB są narysowane poprawnie PDTD R1 = 1kOhm R2 = 10 kOhm PDTB R1 = 4.7 kOhm R2 = 10 KOhm
W sumie to wystarczy przekaźnik SPDT AZ6991-1C-12DE W AVT wygląda rozsądnie bo jest mały Ten co mam jest mniejszy i pożera prąd tylko przy przełączaniu anteny
**Optional inductors
Biasing voltage for active antenna
SMD L2012C
Czy nie powinno być z masy analogowej
VMusic3 i MonkeyBoard powinno dać radę być zasilane na samym tranzystorze NPN (MMBT2222A). Takie rozwiązanie było na stronie: https://github.com/retrojdm/VMusic3 gdzie koleś zasilał VMusic z BC548, a może BC337
SPRAWDZIĆ WYPROWADZENIA 4052N
4052 AB multiplexer setup: B A Output_XY 0 0 0 0 1 1 1 0 2 1 1 3 Najlepiej wersja 74HC4052
VM3_CTS
BR_CTS
BR_RTS
Sprawdzić czy na zasilaniu będzie +3v3
Czy nie można zrezygnować z diody zenera"???
Zener diode + R38 or Le33CZ
JEŚLI NIE BĘDZIE DIZÓAŁĆ MONKEYBOARD TO zmienić rezystoruy na 1 k i 2 k
